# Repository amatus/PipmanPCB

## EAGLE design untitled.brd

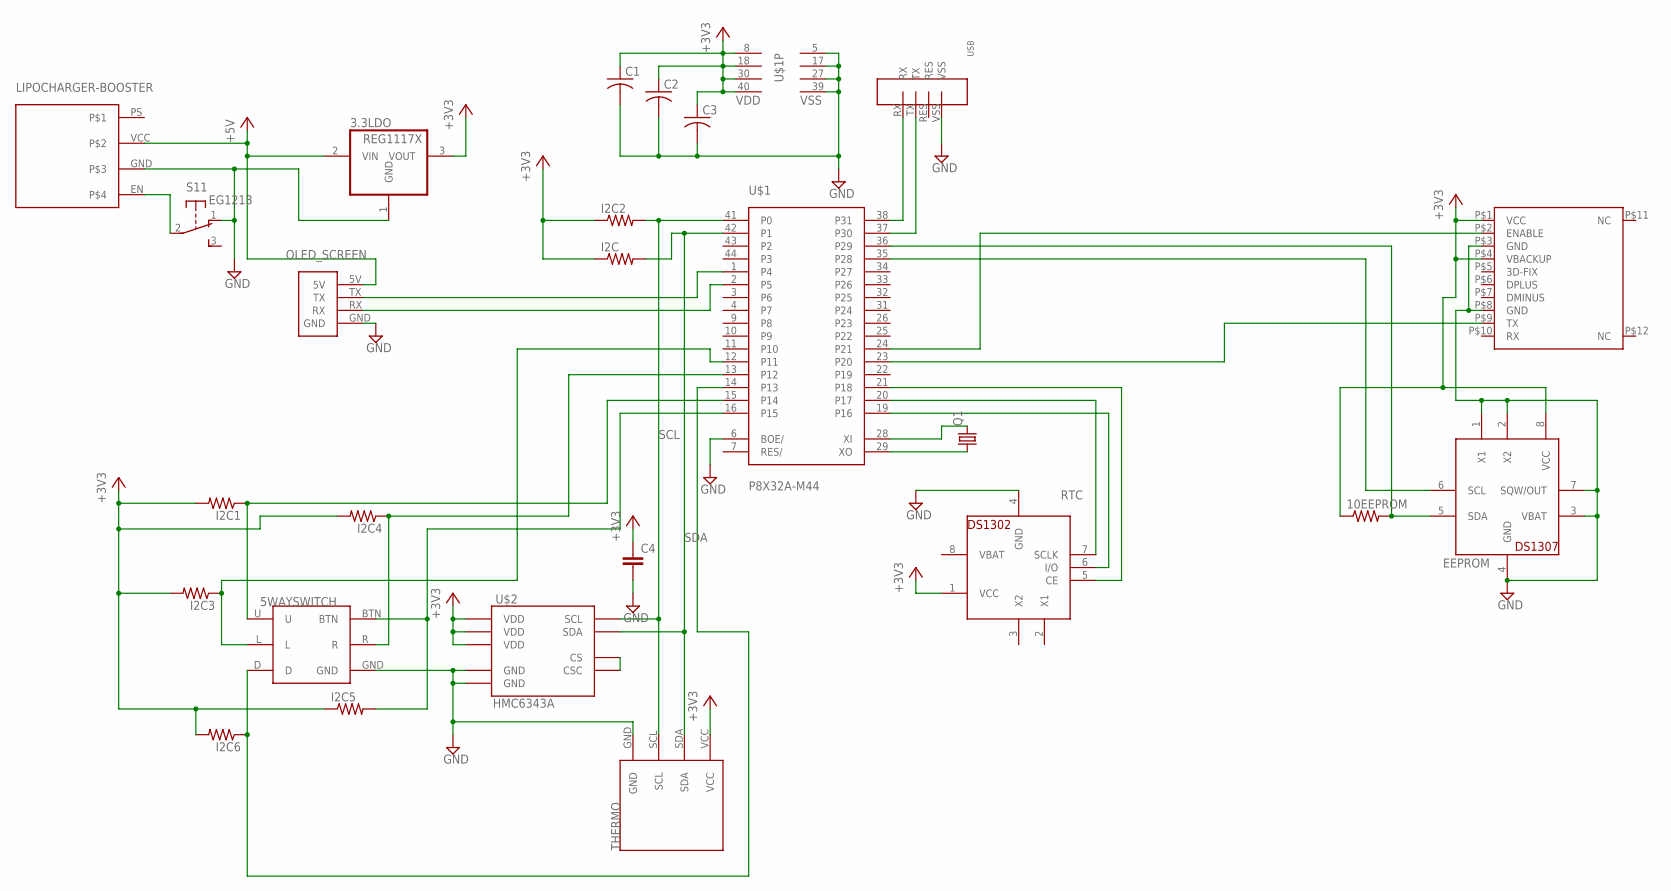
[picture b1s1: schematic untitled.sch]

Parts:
3.3LDO: REG1117X; TO252
5WAYSWITCH: 5-WAYSWITCH
10EEPROM: R-US_R1005; R1005
C1, C2, C3: C-USC0603; C0603
C4: CAP0603; 0603
EEPROM: DS1307; DIL08
GPS: GPS_FGPMMOPA6B; FGPMMOPA6B
I2C, I2C1, I2C2, I2C3, I2C4, I2C5, I2C6: R-US_R1005; R1005
LIPOCHARGER-BOOSTER: SFLIPO
OLED_SCREEN: 4DSCREEN
Q1: CRYSTALHC49S; HC49/S
RTC: DS1302; DIL08-ROUND
S1: EG1213
THERMO: SFTEMP
U$1: P8X32A-M44
U$2: HMC6343A; LCC36
USB: 4PINUSB

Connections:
+3V3: 3.3LDO.3 (VOUT), 10EEPROM.1, C1.1, C2.1, C3.1, C4.1, EEPROM.8 (VCC), GPS.P$1 (VCC), GPS.P$4 (VBACKUP), I2C.1, I2C1.2, I2C2.1, I2C3.2, I2C4.2, I2C5.1, I2C6.2, RTC.1 (VCC), THERMO.VCC, U$1.8 (VDD), U$1.18 (VDD), U$1.30 (VDD), U$1.40 (VDD), U$2.3 (VDD), U$2.11 (VDD), U$2.21 (VDD)
+5V: 3.3LDO.2 (VIN), LIPOCHARGER-BOOSTER.VCC, OLED_SCREEN.5V
GND: 3.3LDO.1 (GND), 5WAYSWITCH.GND, C1.2, C2.2, C3.2, C4.2, EEPROM.1 (X1), EEPROM.2 (X2), EEPROM.3 (VBAT), EEPROM.4 (GND), EEPROM.7 (SQW/OUT), GPS.P$3 (GND), GPS.P$8 (GND), LIPOCHARGER-BOOSTER.GND, OLED_SCREEN.GND, RTC.4 (GND), S1.1 (O), THERMO.GND, U$1.5 (VSS), U$1.6 (BOE/), U$1.17 (VSS), U$1.27 (VSS), U$1.39 (VSS), U$2.25 (GND), U$2.29 (GND), USB.VSS
unnamed: Q1.2, U$1.28 (XI)
unnamed: Q1.1, U$1.29 (XO)
unnamed: GPS.P$9 (TX), U$1.23 (P20)
unnamed: GPS.P$2 (ENABLE), U$1.24 (P21)
unnamed: RTC.5 (CE), U$1.21 (P18)
unnamed: RTC.6 (I/O), U$1.19 (P16)
unnamed: U$1.38 (P31), USB.RX
unnamed: RTC.7 (SCLK), U$1.20 (P17)
unnamed: U$1.37 (P30), USB.TX
unnamed: OLED_SCREEN.RX, U$1.2 (P5)
unnamed: OLED_SCREEN.TX, U$1.1 (P4)
unnamed: LIPOCHARGER-BOOSTER.EN, S1.2
unnamed: 5WAYSWITCH.U, I2C1.1, U$1.15 (P14)
unnamed: 5WAYSWITCH.D, I2C6.1, U$1.14 (P13)
unnamed: 5WAYSWITCH.L, I2C3.1, U$1.12 (P11)
unnamed: 10EEPROM.2, EEPROM.5 (SDA), U$1.36 (P29)
unnamed: EEPROM.6 (SCL), U$1.35 (P28)
unnamed: 5WAYSWITCH.R, I2C4.1, U$1.13 (P12)
unnamed: 5WAYSWITCH.BTN, I2C5.2, U$1.16 (P15)
unnamed: U$2.22 (CS), U$2.35 (CSC)
SCL: I2C2.2, THERMO.SCL, U$1.41 (P0), U$2.32 (SCL)
SDA: I2C.2, THERMO.SDA, U$1.42 (P1), U$2.36 (SDA)
VBAT: RTC.8 (VBAT)

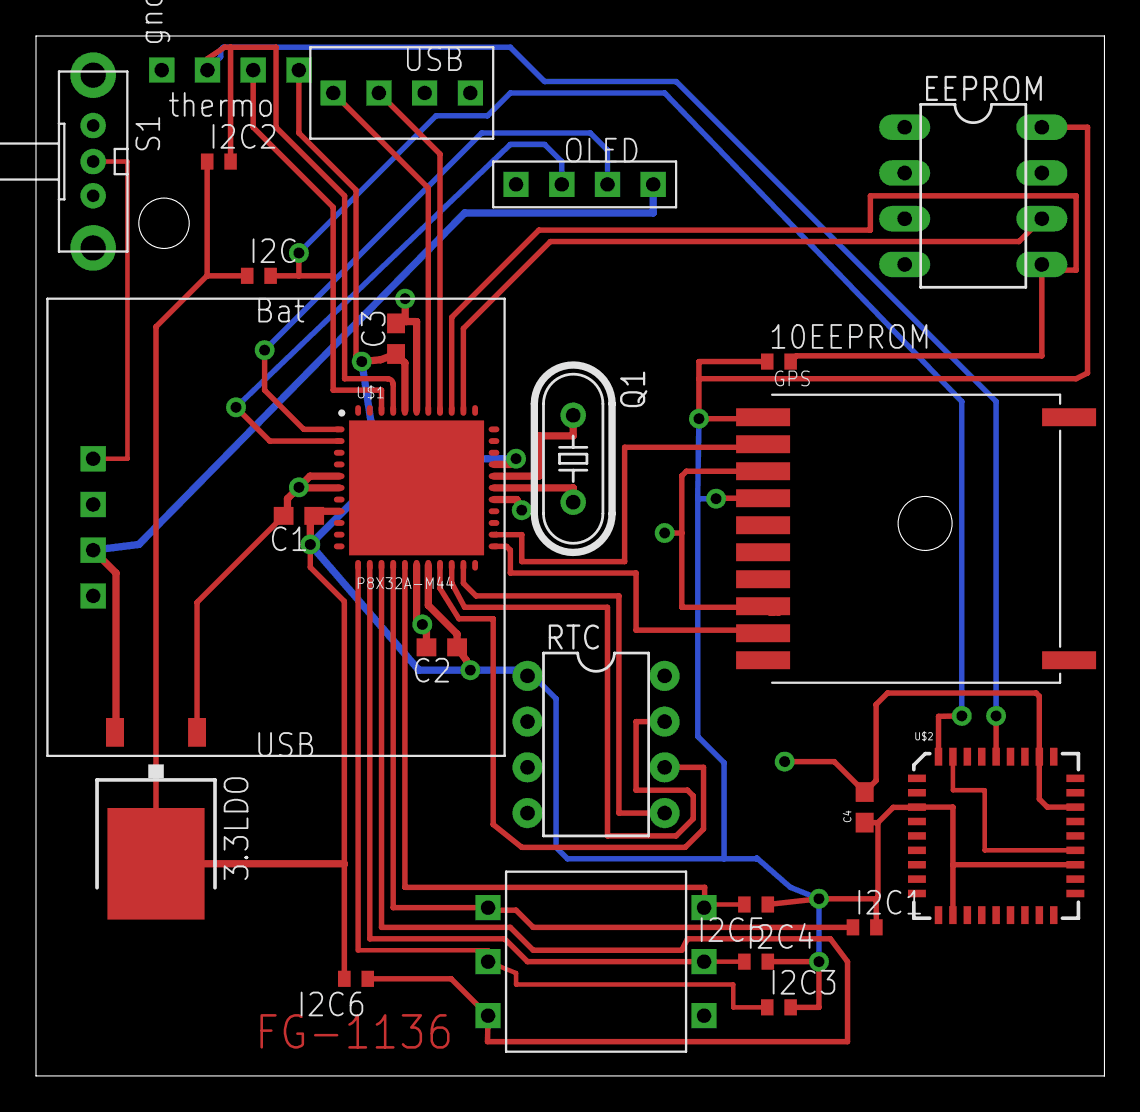
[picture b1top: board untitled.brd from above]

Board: 2 copper layers, 59.4 x 57.8 mm, 25 parts (0 on the bottom side), 25 nets.

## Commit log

2014-09-30 Added
2014-10-05 added power pins
2014-10-05 used sane resistors
2014-10-07 replaced compass break out with raw part
2014-10-07 Add .gitignore to ignore backup files
2014-10-07 Add missing junctions to schematic
2014-10-07 Board cleanup
    * Removed traces to nowhere
    * Made all vias round
    * Optimized some traces to remove vias
    * Made better connections to SMT pads
    * Connected missing ground on compass
2014-10-08 Add supply symbols, didn't fix board
2014-10-08 Added power and decoupling caps to schematic
2014-10-08 Connected BOEn to GND
2014-10-08 Routed some power and decoupling caps
2014-10-14 Finished PCB V2
2014-10-14 fixed shorted caps
2014-10-15 cleaned
2014-10-15 Reconnect GND to OLED header
2014-10-15 Use regulator part from eagle library
2014-10-15 DRC cleanup
2014-10-15 Lots of improvements
2014-10-21 more clean up, with work based off amatus's designs
2014-10-21 fixed clearance issue
2014-10-21 made the traces look better
2014-10-21 Redo crazy snaking +3V3 trace.
2014-10-21 Fix overlapping trace
2014-10-21 Center and rectify traces to the propeller
2014-10-22 made larger battery hole and straightened some traces
